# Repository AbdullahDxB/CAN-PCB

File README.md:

<h1 align="center">CAN Bus MCP2518 Transceiver Node</h1>

<p align="center">
  <b>High-Integrity Industrial Communication Board</b><br>

</p>

<div align="center">
  
  **[View the 3D Board Render](./docs/3DVIEW.png)** &nbsp;&nbsp;•&nbsp;&nbsp; **[View Complete Schematic (PDF)](./docs/Schematic.pdf)**

</div>

---

## 🎯 Project Overview

A robust, two-layer CAN bus transceiver node designed for high-noise industrial environments. Built around the **MCP2518**, this board facilitates reliable, high-speed differential communication. The project demonstrates a strict adherence to layout guidelines, differential pair routing, and rigorous design rule checking (DRC).

## 🛠️ Hardware & Design Stack

* **Transceiver IC:** MCP2518
* **Protocol:** Controller Area Network (CAN)
* **EDA Tool:** KiCAD 9.0 (Schematic Capture, PCB Layout, 3D Rendering)
* **Manufacturing Prep:** Gerber Generation, BOM Management

---

## ⚙️ Design Challenges & Hardware Architecture

1. **Custom Footprint Engineering:** Discovered a critical discrepancy between the default KiCAD footprint library and the manufacturer's datasheet for the transceiver IC. To prevent solder bridging and assembly failure, I manually cross-referenced the physical dimensions and designed a custom footprint from scratch, validating pad spacing against strict DRC parameters.
2. **Differential Pair Routing:** CAN High (CANH) and CAN Low (CANL) traces were strictly routed as differential pairs, ensuring matched impedance and minimizing electromagnetic interference (EMI) in noisy industrial settings.
3. **Design Validation:** Zero errors on both the Electrical Rules Check (ERC) and Design Rules Check (DRC) prior to generating final production files.

---

## 📂 Repository Structure

* **[`hardware/`](./hardware):** Core KiCAD 9.0 project files (`.kicad_sch`, `.kicad_pcb`, `.kicad_pro`).
* **[`docs/`](./docs):** High-resolution schematic PDFs, top/bottom layer copper exports, 3D board renders, and DRC/ERC reports.
* **[`manufacturing/`](./manufacturing):** Generated Bill of Materials (BOM) and production-ready Gerber files.
* **[`datasheets/`](./datasheets):** Component reference documentation.

---
*Created by Abdullah Ajmal - August 2026*

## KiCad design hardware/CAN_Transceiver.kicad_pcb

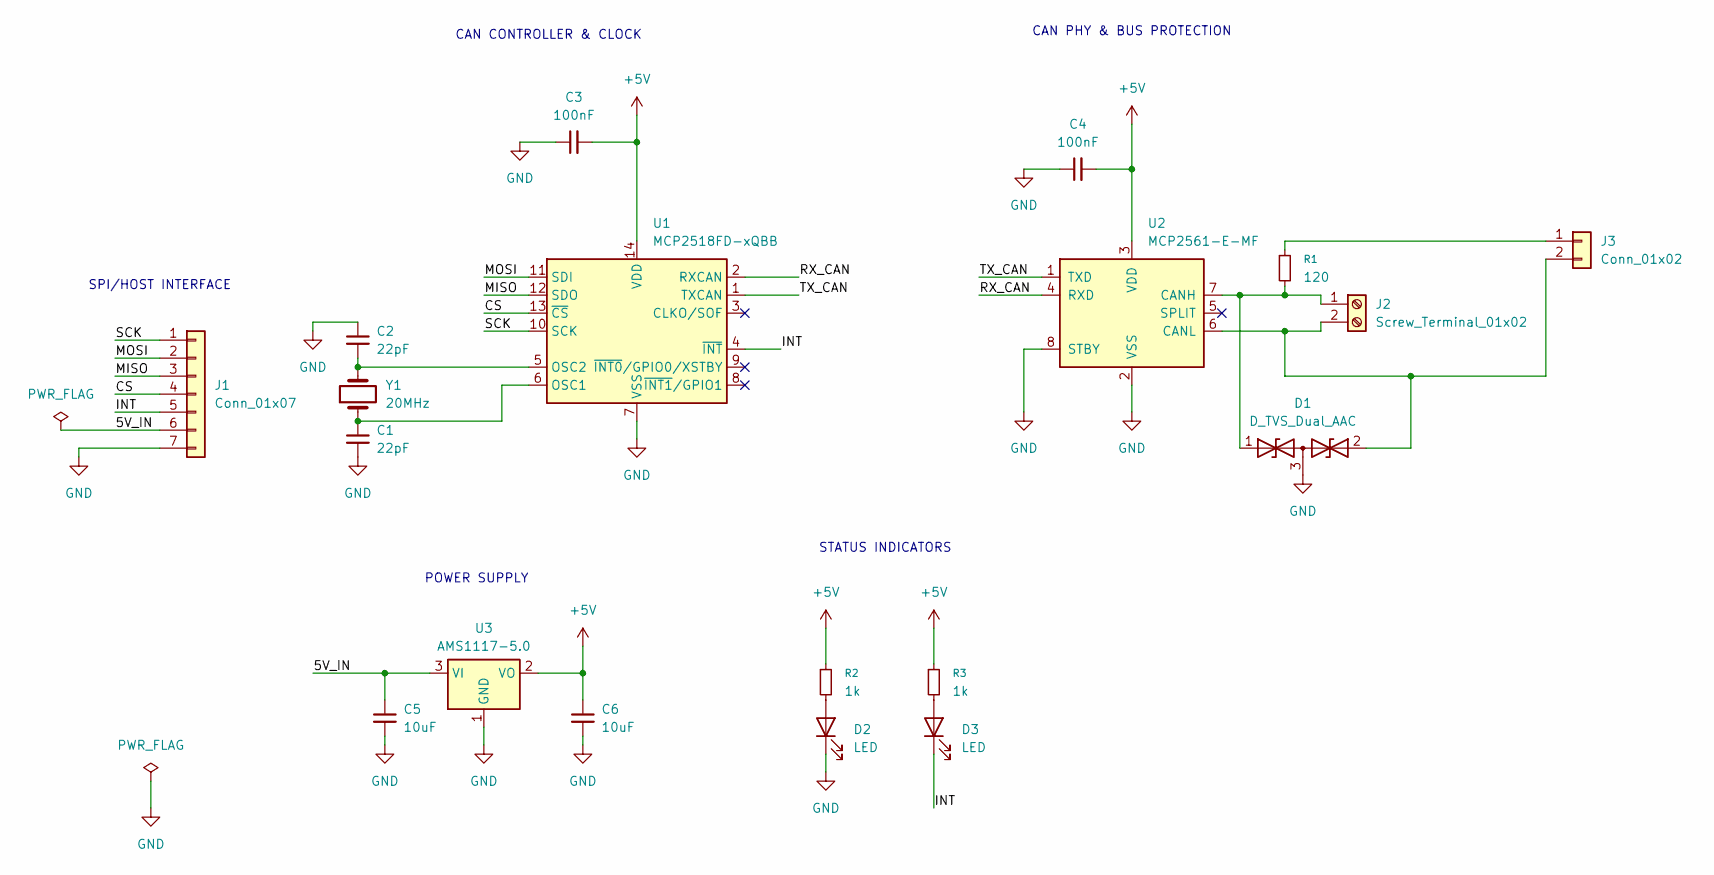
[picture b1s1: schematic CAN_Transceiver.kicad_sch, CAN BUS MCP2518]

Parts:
C1, C2: 22pF; C_0805_2012Metric
C3, C4: 100nF; C_0805_2012Metric
C5, C6: 10uF; C_0805_2012Metric
D1: D_TVS_Dual_AAC; SOT-23
D2, D3: LED; LED_0805_2012Metric
J1: Conn_01x07; PinHeader_1x07_P2.54mm_Vertical
J2: Screw_Terminal_01x02; TerminalBlock_Phoenix_MKDS-1,5-2-5.08_1x02_P5.08mm_Horizont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
J3: Conn_01x02; PinHeader_1x02_P2.54mm_Vertical
R1: 120; R_0805_2012Metric
R2, R3: 1k; R_0805_2012Metric
U1: MCP2518FD-xQBB; SOIC-14_3.9x8.7mm_P1.27mm
U2: MCP2561-E-MF; SOIC-8_3.9x4.9mm_P1.27mm
U3: AMS1117-5.0; SOT-223-3_TabPin2
Y1: 20MHz; Crystal_SMD_HC49-SD

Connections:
+5V: C3.2, C4.2, C6.1, R2.1, R3.1, U1.14 (VDD), U2.3 (VDD), U3.2 (VO)
/5V_IN: C5.1, J1.6, U3.3 (VI)
/CS: J1.4, U1.13 (~CS)
/INT: D3.1 (K), J1.5, U1.4 (~INT)
/MISO: J1.3, U1.12 (SDO)
/MOSI: J1.2, U1.11 (SDI)
/RX_CAN: U1.2 (RXCAN), U2.4 (RXD)
/SCK: J1.1, U1.10 (SCK)
/TX_CAN: U1.1 (TXCAN), U2.1 (TXD)
GND: C1.2, C2.1, C3.1, C4.1, C5.2, C6.2, D1.3 (common), D2.1 (K), J1.7, U1.7 (VSS), U2.2 (VSS), U2.8 (STBY), U3.1 (GND)
unnamed: D1.1 (A1), J2.1, R1.2, U2.7 (CANH)
unnamed: D1.2 (A2), J2.2, J3.2, U2.6 (CANL)
unnamed: D2.2 (A), R2.2
unnamed: D3.2 (A), R3.2
unnamed: J3.1, R1.1
unnamed: C1.1, U1.6 (OSC1), Y1.1
unnamed: C2.2, U1.5 (OSC2), Y1.2

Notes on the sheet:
CAN CONTROLLER & CLOCK
CAN PHY & BUS PROTECTION
POWER SUPPLY
STATUS INDICATORS
SPI/HOST INTERFACE

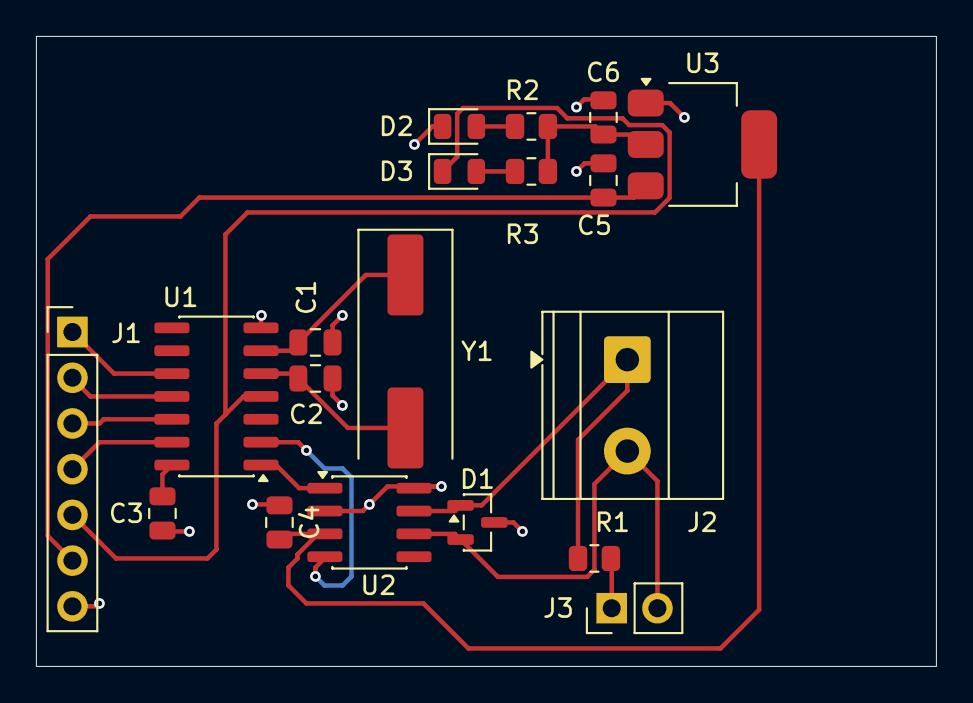
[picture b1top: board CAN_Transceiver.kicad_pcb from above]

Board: 2 copper layers, 50.0 x 35.0 mm, 19 parts (0 on the bottom side), 17 nets.

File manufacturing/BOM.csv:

Reference,Qty,Value,DNP,Exclude from BOM,Exclude from Board,Footprint,Datasheet
"C1,C2",2,22pF,,,,Capacitor_SMD:C_0805_2012Metric,~
"C3,C4",2,100nF,,,,Capacitor_SMD:C_0805_2012Metric,~
"C5,C6",2,10uF,,,,Capacitor_SMD:C_0805_2012Metric,~
D1,1,D_TVS_Dual_AAC,,,,Package_TO_SOT_SMD:SOT-23,~
"D2,D3",2,LED,,,,LED_SMD:LED_0805_2012Metric,~
J1,1,Conn_01x07,,,,Connector_PinHeader_2.54mm:PinHeader_1x07_P2.54mm_Vertical,~
J2,1,Screw_Terminal_01x02,,,,"TerminalBlock_Phoenix:TerminalBlock_Phoenix_MKDS-1,5-2-5.08_1x02_P5.08mm_Horizontal",~
J3,1,Conn_01x02,,,,Connector_PinHeader_2.54mm:PinHeader_1x02_P2.54mm_Vertical,~
R1,1,120,,,,Resistor_SMD:R_0805_2012Metric,~
"R2,R3",2,1k,,,,Resistor_SMD:R_0805_2012Metric,~
U1,1,MCP2518FD-xQBB,,,,Package_SO:SOIC-14_3.9x8.7mm_P1.27mm,https://ww1.microchip.com/downloads/aemDocuments/documents/O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
U2,1,MCP2561-E-MF,,,,Package_SO:SOIC-8_3.9x4.9mm_P1.27mm,http://ww1.microchip.com/downloads/en/DeviceDoc/25167A.pdf
U3,1,AMS1117-5.0,,,,Package_TO_SOT_SMD:SOT-223-3_TabPin2,http://www.advanced-monolithic.com/pdf/ds1117.pdf
Y1,1,20MHz,,,,Crystal:Crystal_SMD_HC49-SD,~
